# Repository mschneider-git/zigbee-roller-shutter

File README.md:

# Zigbee retrofit for a Heim & Haus solar roller shutter (ESP32-H2, Home Assistant ZHA)

Firmware and two PCB designs that add Zigbee to a battery/solar powered roller shutter drive
from **Heim & Haus**. The board plugs onto the 3-pin header of the membrane keypad and "presses"
the UP / DOWN keys electrically. The original controller stays untouched and keeps handling the
motor, its end switches and the solar charging. In Home Assistant the shutter shows up via
**ZHA** as a `cover` entity with open, close, stop and a position slider.

## Features

- Zigbee HA **Window Covering Device** (0x0202): up, down, stop, go to position (%)
- **Time-based position**, calculated from the measured travel times, reported while moving and
  stored in flash
- **Manual operation is tracked**: when someone presses a key on the drive, the firmware reads
  the key line and keeps the position in sync
- **Motor current and motor voltage sensing**: the battery voltage sag shows whether the motor
  really runs, the motor terminal voltage shows whether the controller switched it on. This
  detects the end positions and key presses that the controller took as "stop"
- **Battery and solar panel in Home Assistant**: battery voltage and charge level (battery sensor)
  and the solar panel voltage, measured every 15 minutes at rest
- **Low power**: Zigbee *sleepy end device* with light sleep between polls (peripherals powered
  down, 32 kHz crystal)
- **Zigbee OTA updates** through ZHA, with automatic rollback
- Factory reset: hold **BOOT for 5 s**

## The drive this was developed for

A **Heim & Haus solar roller shutter drive**: the motor, a controller box with a membrane keypad,
a battery pack and a solar panel. Everything below was measured on one of these drives. Other
drives with a similar keypad controller may work, but the travel times, the stop behaviour and the
voltage thresholds have to be checked.

| Controller box with its two keys | Opened: controller board, battery pack on the left |
|---|---|
|  |  |

In the opened box: the 4-pole terminal block at the top (solar panel yellow/black, motor
blue/brown), the white battery plug top right, the relay and the `R020` shunt in the middle, the
PIC below it and the **3-pin keypad header bottom right**, which is where the carrier board plugs on.

| Part | Details |
|---|---|
| Controller | Microchip PIC16F18344 at 3.3 V (HT7533 regulator, about 100 mA, not used for the retrofit) |
| Motor switching | polarity reversal by relay, 20 mOhm shunt (`R020`) in battery−, fuse T5A |
| Terminals | **SG** solar panel (+ yellow, − black), **M** motor (+ blue, − brown), battery via plug (red = +) |
| Keypad | membrane keypad on a 3-pin header (GND · DOWN · UP), keys active low, see below |
| Battery | Cellonic CC-PA000942, 3S Li-ion, 11.1 V nominal, 2600 mAh (28.9 Wh), about 9–12.6 V |
| End positions | detected by the motor itself (it switches off internally) |

Measured behaviour of the controller:

| What | Value |
|---|---|
| Key press needed | 300 ms is enough for UP and DOWN |
| Travel time down / up | 14.2 s / 16.0 s (interrupted runs add up correctly) |
| Stop | press the **opposite** key while moving |
| Run-on after the end position | motor stays powered for about 30 s; a key press in that time is a stop |
| Battery voltage sag while running | 70–92 mV down, 140–200 mV up (battery at about 12.2 V) |
| Motor terminals at rest | both without voltage |
| Sleep of the controller | not observed: a key press after more than 5 min idle works immediately |

The controller sits in a small housing; the lid leaves about 22 mm above the original board, but
only about 6 mm above our carrier board at its left edge, which limits the height of the
H2-Zero (see the [carrier README](hardware/carrier/README.md)).

## How it works

The keypad keys of the original controller (a PIC16F18344 at 3.3 V) are active low with pull-ups
on the controller board. The ESP32-H2 drives the key lines open drain through 1 kOhm, so a
"key press" is just pulling the line low for 300 ms, exactly like the real keypad.

The controller stops a moving motor when the *opposite* key is pressed. After an end position it
keeps the motor powered for about 30 s (run-on); a press during that time acts as stop, not as
start. To handle this reliably the firmware measures:

| Signal | Divider | Used for |
|---|---|---|
| Battery+ | IO4 | motor current (voltage sag 70–200 mV while running), battery level |
| Motor terminal M+ / M− | IO5 / IO1 | controller switched the motor on (one terminal at battery voltage) |
| Solar panel | IO2 | reported to Home Assistant |

All dividers are 1 MOhm / 220 kOhm with 100 nF, about 10 µA from the battery.

**Only the battery and the keypad are required.** The motor terminal and solar inputs are optional
and can stay unconnected:

- Without the **motor terminals** the firmware relies on the battery voltage sag alone. It notices
  the missing terminals on the first move (motor current, but no terminal voltage) and remembers
  that. What is lost: a key press taken as stop during the run-on is only detected after the
  motor current timeout, and a move towards an end position where the shutter already is costs
  extra presses until the firmware gives up.
- Without the **solar panel** no solar voltage is reported to Home Assistant.

## Hardware

The [carrier board](hardware/carrier/README.md) (2 layers, 41.5 × 29.1 mm) plugs onto the keypad
header of the original board; the keypad itself plugs into a 90° header on the carrier, and the red
battery wire is cut and looped through a WAGO 2060 spring terminal. A **Waveshare ESP32-H2-Zero**
is soldered onto it on spacers (USB-C, BOOT and RESET are on the H2-Zero). Everything else
(regulator, protection, dividers, 32 kHz crystal) can be assembled by JLCPCB.

*Render of the carrier board with the H2-Zero (simplified model) soldered on its pin headers.*

GPIO assignment (the firmware defaults):

| Function | GPIO |
|---|---|
| UP key / DOWN key | IO10 / IO11 |
| BOOT (factory reset) | IO9 |
| Dividers battery / M+ / M− / solar | IO4 / IO5 / IO1 / IO2 |
| 32 kHz crystal | IO13 / IO14 |

### Keypad header of the original board

| Pin (from the top) | Function | Level at rest |
|---|---|---|
| top | GND | 0 V |
| middle | DOWN | 3.3 V (pull-up on the controller board) |
| bottom | UP | 3.3 V (pull-up on the controller board) |

**Ground only comes via the keypad header.** Never connect battery− to our GND: the controller
has a 20 mOhm shunt between battery− and its ground, a second connection would bypass it.

## Building and flashing the firmware

Requires [ESP-IDF v6.1](https://docs.espressif.com/projects/esp-idf/en/v6.1/esp32h2/get-started/index.html).
The Zigbee library (esp-zigbee-lib 2.0.4) is fetched from the Espressif Component Registry on the
first build. Note that Espressif officially recommends ESP-IDF v5.5 for the Zigbee SDK.

```bash
idf.py set-target esp32h2
idf.py menuconfig        # "Roller shutter": travel times, GPIOs, stop method ...
idf.py build
idf.py -p /dev/ttyACM0 flash monitor
```

GitHub Actions builds the firmware on every push. `zigbee_roller_shutter_merged.bin` from the
workflow artifacts can be flashed at address `0x0`, e.g. with the
[ESP Web Flasher](https://espressif.github.io/esptool-js/).

## Configuration (menuconfig → Roller shutter)

| Option | Default | Meaning |
|--------|---------|---------|
| Output stage | open drain | direct connection to the keypad lines (low = pressed); push-pull for optocouplers |
| Drive mode | PULSE | simulate a key press; the drive runs to the end position by itself |
| GPIO UP / DOWN | 10 / 11 | bottom / middle keypad pin |
| Stop method | opposite key | as measured on the Heim & Haus drive; alternatives: same key, dedicated key, none |
| Key press duration | 300 ms | |
| Detect manual key presses | on | key presses on the drive itself are tracked |
| Travel time up / down | 16.0 s / 14.2 s | measured on the drive |
| Dividers battery / M+ / M− / solar | GPIO 4 / 5 / 1 / 2 | −1 = not fitted. Unconnected motor terminals are detected on the first move, an unconnected solar input is not reported |
| Motor current via battery voltage | on | checks that the motor starts and detects the end position; time-based only without divider |
| Motor current step threshold | 50 mV | measured: 70–92 mV sag down, 140–200 mV up, noise ±10 mV |
| Motor voltage threshold | 6000 mV | both motor terminals are without voltage at rest |
| Battery empty / full | 9.6 V / 12.6 V | for the charge level (3S Li-ion, linear) |
| Measurement interval at rest | 900 s | battery and solar panel |
| Poll interval | 1000 ms | response time vs. current (end device), under *Roller shutter Zigbee* |

## Adding it to Home Assistant (ZHA)

1. Flash the firmware and install the board. A factory-new device searches for a network by itself.
2. In Home Assistant: *Settings → Devices & services → ZHA → Add device*.
3. The device appears as `DIY ESP32H2-Shutter` with a **cover** entity, a battery sensor and the
   solar voltage (Analog Input).
4. **Calibrate:** run the shutter fully up once. Every move into an end position resynchronises
   the calculated position.

To pair again: hold BOOT for 5 s (factory reset) or remove the device in ZHA.

## Firmware updates over Zigbee (OTA)

The first flash has to be done over USB because of the partition table (`ota_0` + `ota_1`).

**Increase the version:** `PROJECT_VER` in `CMakeLists.txt` (form `x.y.z`). It yields the OTA file
version (`1.2.3` → `0x01020300`, must increase with every update) and the version shown in ZHA.
Every build also produces `build/131B-5201-<version>-ota-file.zigbee`, which is also a CI artifact.

**Set up Home Assistant once** (`configuration.yaml`, then restart):

```yaml
zha:
  zigpy_config:
    ota:
      extra_providers:
        - type: advanced
          warning: "I understand I can *destroy* my devices by enabling OTA updates from files. Some OTA updates can be mistakenly applied to the wrong device, breaking it. I am consciously using this at my own risk."
          path: /config/zigpy_ota
```

**Install an update:** copy the `.zigbee` file to `/config/zigpy_ota`. The device asks for updates
at start-up and every 24 h; ZHA then shows an update entity. As a sleepy end device the download
takes about 10–20 minutes, then the device restarts.

**Safety net:** a new image only boots on trial. It becomes valid once it has rejoined the Zigbee
network; if it crashes before that, the next reset boots the previous version.

## Project status

- The control logic (key pulses, stop by opposite key, run-on handling, battery-sag detection)
  was developed and measured on the real drive with a bench setup.
- The ESP32-H2 boards have not been built and tested yet. Sleep current, OTA and the motor
  voltage sensing are untested on real hardware.
- Positions between the end positions are estimated from the travel times.

## Project structure

```
main/main.c                 Zigbee: device, commissioning, Window Covering commands -> shutter
main/ota.c                  Zigbee OTA client (download, rollback confirmation, periodic query)
main/ota_file_parser.c      parser for the Zigbee OTA file format (from the esp-zigbee-sdk example)
main/Kconfig.projbuild      Zigbee and OTA settings
tools/image_builder_tool.py creates the OTA file (from the esp-zigbee-sdk)
components/shutter/         roller shutter logic without Zigbee
  shutter.c                 state machine, key pulses, position tracking, NVS
  inputs.c                  BOOT button (factory reset) and detection of manual operation
  sense.c                   voltage sensing: battery, motor terminals, solar (ADC, own dividers)
  Kconfig                   roller shutter settings
hardware/carrier/           carrier board for the ESP32-H2-Zero (KiCad 10, generated by script)
hardware/lib/               project footprint and 3D model, their generator and the routing steps
hardware/fab.py             Gerber, BOM and placement files for JLCPCB
docs/                       photos of the original controller, renders of the carrier board
```

## License

[MIT](LICENSE), except for the following files taken from Espressif's
[esp-zigbee-sdk](https://github.com/espressif/esp-zigbee-sdk) examples, which are in the public
domain / CC0: `main/ota_file_parser.c`, `main/ota_file_parser.h`, `tools/image_builder_tool.py`.

The boards use footprints from the KiCad standard library (CC-BY-SA 4.0 with an exception that
allows their use in your own designs) and a footprint generated by `hardware/lib/make_footprints.py`.

This is an independent hobby project, not affiliated with Heim & Haus. Modifying the drive is at
your own risk: you are working on a battery-powered device with a motor.

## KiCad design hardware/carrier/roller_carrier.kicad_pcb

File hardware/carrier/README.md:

# Carrier board Roller-H2 Zero v2

2-layer board (41.5 × 29.1 mm, U-shaped) that plugs directly onto the 3-pin keypad header of the
original controller board. A **Waveshare ESP32-H2-Zero** sits on spacers above the regulator and
dividers and is soldered in by hand; JLCPCB can assemble everything else.

| Top | Bottom |
|---|---|
|  |  |

The H2-Zero in the renders is a simplified model generated by `../lib/make_footprints.py`
from the product photos. For J1 the renders use WAGO's 3D model of the 2060-452/998-404 (from
WAGO's CAD download, not included here because of its terms of use); the board itself references
a simplified model of the terminal from the same script.

## Connectors

| Ref | What | Position |
|---|---|---|
| J6 / J7 | 1×9 holes for the H2-Zero (soldered by hand), **USB-C up**, antenna down | left |
| J3 | 1×3 socket, **bottom side**, onto the original keypad header (GND · DOWN · UP) | bottom right |
| J4 | 1×3 header, 90°, membrane keypad, pins towards the board centre, GND on top | bottom right |
| J1 | WAGO 2060-452, **battery+ looped through**: cut the red battery wire and put both ends into the two spring terminals | right arm, wire entry at the top |
| J5 | 1×3 header, 90°, measurement inputs **SOL · M+ · M−** (labels on the bottom side), **optional**, see below | left arm, pins pointing up |

USB-C, BOOT and RESET are on the H2-Zero itself.

## Circuit

USB-C, ESD protection, BOOT/RESET and the EN circuit are on the H2-Zero.

- **Battery+ (VBAT_RAW)** → PTC 100 mA (F1) → **reverse polarity protection** P-MOSFET AO3407A
  (Q1, gate via 100 kΩ to GND) → VBAT → 10 Ω (R1) → VIN.
  The two WAGO poles are connected by a copper area on both layers; the motor current only flows
  through this area, not through the electronics.
- **VIN**: TVS SMF13A (D1) against spikes from the motor, 10 µF (C1) → **TPS629203** (U1) → 3.3 V
  to the **3V3 pin** of the H2-Zero. VSET open = 3.3 V, MODE 64.9 kΩ = auto PFM/PWM 1 MHz,
  EN (pin 7) to VIN, PG open. The 5V pin of the H2-Zero stays open.
- **Dividers** 1 MΩ / 220 kΩ / 100 nF each (factor 5.55, 12.6 V → 2.27 V): battery (after the
  reverse polarity protection), motor+, motor−, solar.
- **Keys**: DOWN/UP each via 1 kΩ to the H2-Zero, connected 1:1 between J3 and J4.
- **32 kHz crystal** Y1 (CL 12.5 pF) with C11/C12 (18 pF each) on IO13/IO14.
- Regulator and dividers sit **below the H2-Zero**. There is no copper on either layer below its
  ceramic antenna (bottom end, at the board edge).
- Ground only via J3 (keypad GND). **Do not connect battery−** (20 mΩ shunt on the original board).

### GPIO assignment

Matches the firmware defaults:

| Signal | GPIO | Row / pin |
|---|---|---|
| Battery (divider) | IO4 | J6 / 8 |
| Motor+ (divider) | IO5 | J6 / 9 |
| Motor− (divider) | IO1 | J6 / 5 |
| Solar (divider) | IO2 | J6 / 6 |
| UP key | IO10 | J7 / 9 |
| DOWN key | IO11 | J7 / 8 |
| 32 kHz crystal | IO13 / IO14 | J7 / 6, 5 |
| 3V3 / GND | – | J6 / 3, 2 |

## Mounting the H2-Zero and height

The H2-Zero is soldered **directly into J6/J7** with its pin headers. The plastic strip of the
header (about 2.5 mm) acts as spacer: the regulator and dividers sit below it, the tallest part
is the inductor L1 at 1.2 mm.

- Height above the board: 2.5 mm spacer + 1 mm H2-Zero board + about 3.2 mm USB-C connector ≈ 6.7 mm.
- In the housing of the Heim & Haus controller there are only about 6 mm free above the board at the left edge.
  **Check before soldering** that the lid closes; if needed, shorten the plastic strip (leave at
  least 1.5 mm above L1).
- Cut the pins flush on the bottom side: J3 plugs onto the keypad header there.

## Preparing the H2-Zero

1. **Flash it before soldering** via its USB-C. Later, flash over USB only **without battery**
   (J1 open), otherwise its LDO and the TPS629203 feed the 3V3 rail at the same time. Further
   updates via Zigbee OTA.
2. **Remove the RGB LED (IO8)**: it draws 0.5–1 mA even when off.
3. The H2-Zero's LDO (ME6217) is back-fed via 3V3 and draws around 50 µA according to its
   datasheet. **Measure the sleep current**; if it is clearly too high, remove the LDO before
   soldering (USB flashing then only works with the battery connected, OTA is unaffected).

## Generating and checking

```bash
python3 make_board.py                         # placement, nets, silkscreen
python3 route.py /path/to/freerouting.jar     # Freerouting, GND areas, DRC (up to 5 attempts)
python3 ../fab.py carrier                     # fab/gerber.zip, bom_jlc.csv, cpl_jlc.csv
```

`route.py` always starts from a fresh `make_board.py`. Freerouting (2.x, needs Java) does not give
the same result on every run and occasionally hangs; the script checks every attempt with the DRC
and routes again up to five times. A run takes 2–7 minutes.

Expected: 0 DRC errors, 0 unconnected items. The remaining "silk_edge_clearance" warnings are
intended (header pins protrude over the edge).

## Ordering at JLCPCB

1. Upload `fab/gerber.zip`, 2 layers, 1.6 mm.
2. PCB Assembly (Economic), **Assembly side: Top**, `fab/bom_jlc.csv` and `fab/cpl_jlc.csv`.
   All parts are regular JLCPCB stock, no Global Sourcing needed. JLCPCB solders the 90° headers
   J4 and J5 (C92159) by hand. J3 (8.5 mm socket, C42431866) is in the BOM/CPL but sits on the
   **bottom side**: with "Assembly side: Top", JLCPCB leaves it out (Economic assembles one side only).
3. In the placement preview, check the rotation of **U1** (SOT-583, pin 1 = FB/VSET), **Q1**,
   **J1** (wire entry up), **J4** (pins towards the board centre) and **J5** (pins up).

## Assembly by hand

1. If J3 is not fitted: solder a 1×3 socket (8.5 mm) from the **bottom side**, opening away from
   the board. Plug it onto the keypad header of the original board to align it, then solder.
2. **Measure before soldering the H2-Zero**: battery on J1 → 3.3 V at J6 pin 3, ≈ 2.2 V at
   J6 pin 8 (IO4) with a 12.2 V battery.
3. Solder the H2-Zero (flashed, RGB LED removed) with its pin headers on spacers into J6/J7,
   **USB-C towards the "USB" label**. Cut the pins flush on the bottom side.
4. Cut the red battery wire, put both ends into J1, plug the board onto the keypad header and the
   keypad into J4.
5. Optional: connect J5 to the controller's terminal block, SOL to solar + (yellow), M+ and M− to
   the motor terminals (blue, brown). Without these wires the firmware works with the battery
   voltage alone (see the main README).

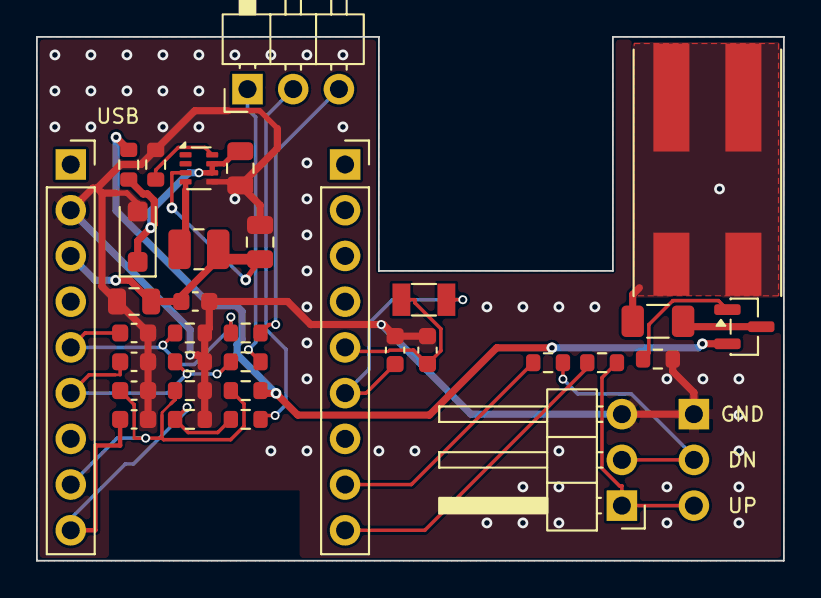
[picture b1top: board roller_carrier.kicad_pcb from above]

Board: 2 copper layers, 41.5 x 29.1 mm, 35 parts (1 on the bottom side), 22 nets.

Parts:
C1: 10u 25V; C_0805_2012Metric
C2: 22u; C_0805_2012Metric
C4: 10u; C_0805_2012Metric
C5, C7, C8, C9, C10: 100n; C_0603_1608Metric
C11, C12: 18p; C_0603_1608Metric
D1: SMF13A; D_SOD-123F
F1: PTC 100mA; Fuse_1206_3216Metric
J1: WAGO 2060-452 battery+; WAGO_2060-452
J3: to keypad header; PinSocket_1x03_P2.54mm_Vertical
J4: Membrane keypad; PinHeader_1x03_P2.54mm_Horizontal
J5: Solar M+ M-; PinHeader_1x03_P2.54mm_Horizontal
J6: H2-Zero soldered left; PinSocket_1x09_P2.54mm_Vertical
J7: H2-Zero soldered right; PinSocket_1x09_P2.54mm_Vertical
L1: 2.2u; L_1008_2520Metric
Q1: AO3407A; SOT-23
R1: 10; R_0603_1608Metric
R2: 64.9k; R_0603_1608Metric
R5: 100k; R_0603_1608Metric
R8, R9: 1k; R_0603_1608Metric
R12, R14, R16, R18: 1M; R_0603_1608Metric
R13, R15, R17, R19: 220k; R_0603_1608Metric
U1: TPS629203DRLR; SOT-583-8
Y1: 32.768k; Crystal_SMD_3215-2Pin_3.2x1.5mm

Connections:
+3V3: C2.1, C4.1, C5.1, J6.3, L1.2, U1.3
ADC_BAT: C7.1, J6.8, R12.2, R13.1
ADC_MM: C9.1, J6.5, R16.2, R17.1
ADC_MP: C8.1, J6.9, R14.2, R15.1
ADC_SOL: C10.1, J6.6, R18.2, R19.1
DOWN: J3.2, J4.2, R8.2
GATE: Q1.1, R5.1
GND: C1.1, C2.2, C4.2, C5.2, C7.2, C8.2, C9.2, C10.2, C11.2, C12.2, D1.2, J3.1, J4.3, J6.2, R2.2, R5.2, R13.2, R15.2, R17.2, R19.2, U1.5
IO10: J7.9, R9.1
IO11: J7.8, R8.1
MM: J5.3, R16.1
MODE: R2.1, U1.8
MP: J5.2, R14.1
SOL: J5.1, R18.1
SW: L1.1, U1.4
UP: J3.3, J4.1, R9.2
VBAT: Q1.2, R1.2, R12.1
VBAT_F: F1.2, Q1.3
VBAT_RAW: F1.1, J1.1, J1.2
VIN: C1.2, D1.1, R1.1, U1.6, U1.7
XTAL_N: C12.1, J7.5, Y1.2
XTAL_P: C11.1, J7.6, Y1.1

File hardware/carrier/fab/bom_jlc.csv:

Comment,Designator,Footprint,LCSC Part #
10u 25V,C1,C_0805_2012Metric,C15850
100n,"C10,C5,C7,C8,C9",C_0603_1608Metric,C14663
18p,"C11,C12",C_0603_1608Metric,C1647
22u,C2,C_0805_2012Metric,C784585
10u,C4,C_0805_2012Metric,C15850
SMF13A,D1,D_SOD-123F,C353315
PTC 100mA,F1,Fuse_1206_3216Metric,C70065
WAGO 2060-452 battery+,J1,WAGO_2060-452,C2765055
to keypad header,J3,PinSocket_1x03_P2.54mm_Vertical,C42431866
Membrane keypad,J4,PinHeader_1x03_P2.54mm_Horizontal,C92159
Solar M+ M-,J5,PinHeader_1x03_P2.54mm_Horizontal,C92159
2.2u,L1,L_1008_2520Metric,C237482
AO3407A,Q1,SOT-23,C15155
10,R1,R_0603_1608Metric,C22859
1M,"R12,R14,R16,R18",R_0603_1608Metric,C22935
220k,"R13,R15,R17,R19",R_0603_1608Metric,C22961
64.9k,R2,R_0603_1608Metric,C2960807
100k,R5,R_0603_1608Metric,C25803
1k,"R8,R9",R_0603_1608Metric,C21190
TPS629203DRLR,U1,SOT-583-8,C5219295
32.768k,Y1,Crystal_SMD_3215-2Pin_3.2x1.5mm,C620155
